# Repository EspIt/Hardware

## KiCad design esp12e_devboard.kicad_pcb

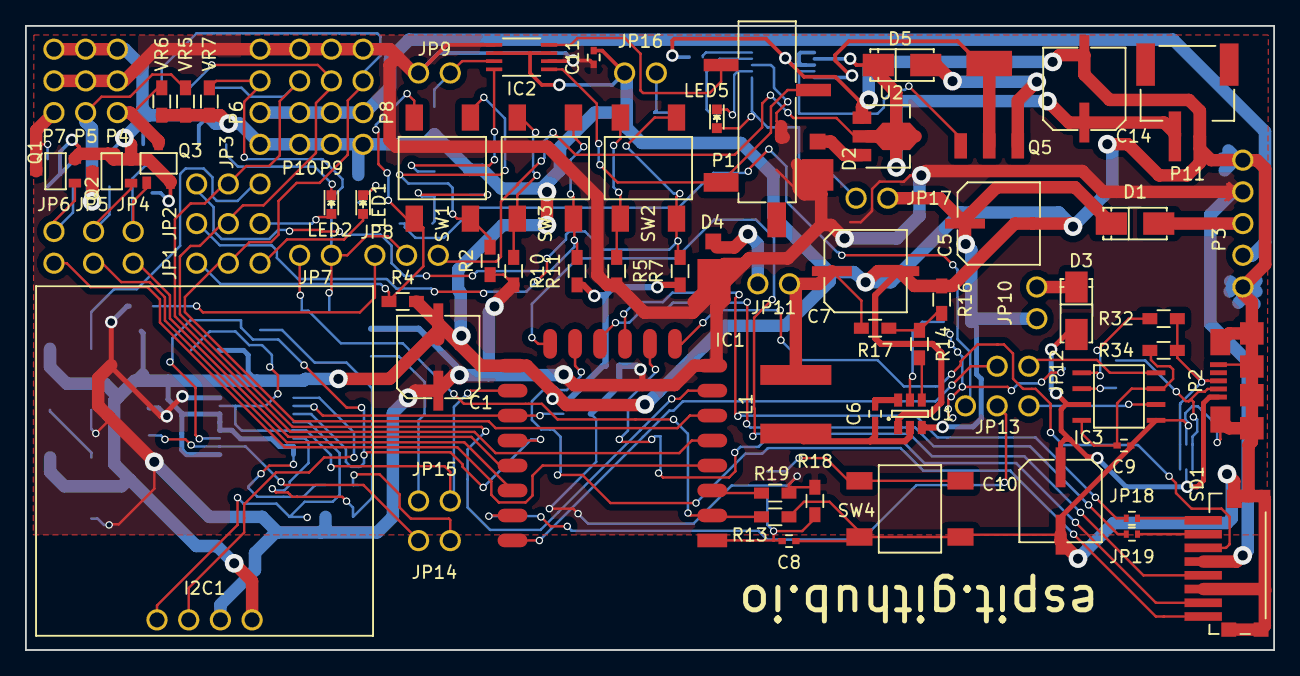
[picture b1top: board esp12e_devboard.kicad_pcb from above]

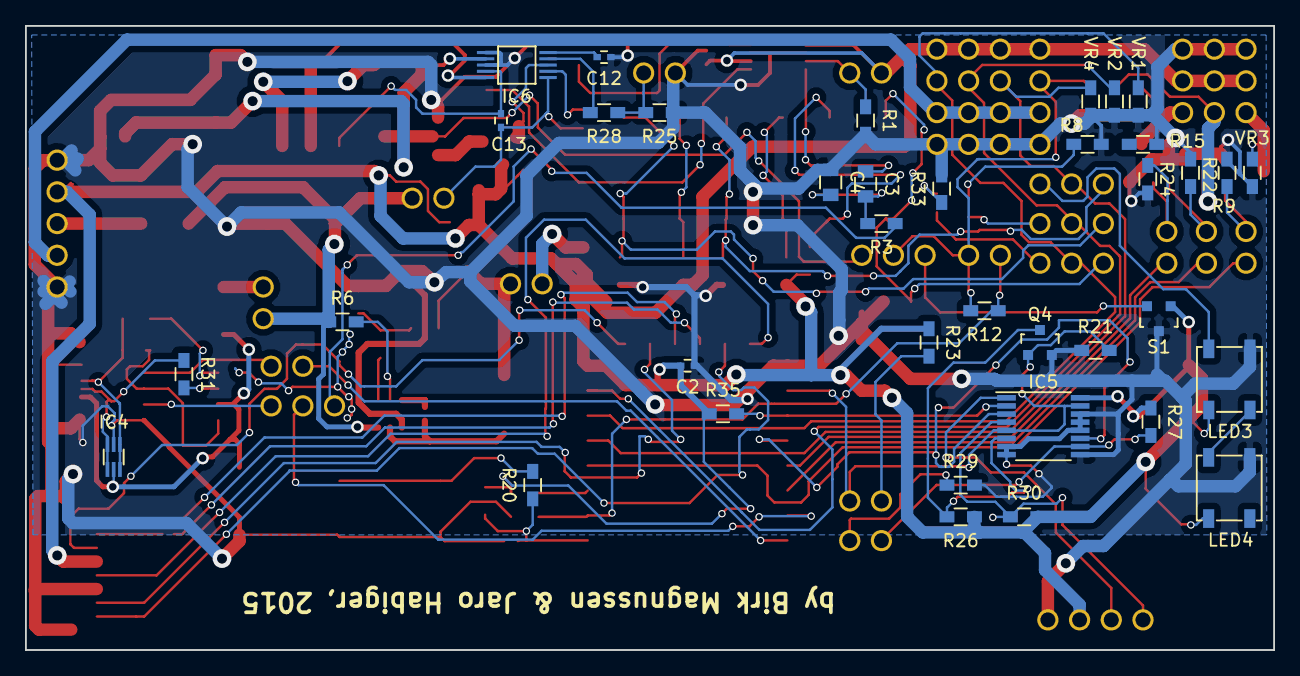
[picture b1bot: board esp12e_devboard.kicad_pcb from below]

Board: 2 copper layers, 100.0 x 50.0 mm, 117 parts (37 on the bottom side), 86 nets.

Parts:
C1, C5, C7, C10, C14: UWT1E101MCL1GS; UWT1E101MCL1GS_N
C2, C6, C8, C9, C11: CL05A105JQ5NNNC; C_0402
C3: CL21F334ZBFNNNE; C_0805
C4: FCA0805C104M-J2; C_0805
C12, C13: 100n_0603; C_0402
D1, D3, D5: SK34A-LTP; DO-214AC_N
D2, D4: UPS115UE3/TR7CT-ND; UPS115UE3_TR7
I2C1: IIC Serial 128X64; i2c
IC1: ESP12E
IC2: LM4906MM/NOPB; VSSOP-8_N
IC3: PL2303SA; SOP8
IC4: USBLC6_2SC6; SOT-666_N
IC5: CD74HC4316PWR; TSSOP-16_4.4x5mm_Pitch0.65mm
IC6: MAX1898EUB42; µMax
JP1, JP2, JP3, JP8, JP13: JUMPER3; Conn_3
JP4, JP5, JP6, JP7, JP9, JP10, JP11, JP12, JP14, JP15, JP16, JP17: JUMPER; Conn_2
JP18, JP19: 0; R_0402
L1: NR6028T4R7M
LED1, LED2, LED5: LED_0603; LED-0603
LED3, LED4: WS2812B; 5050
P1: SJ-3523-SMT-TR; SJ-3523-SMT-TR_N
P2: 10118192-0001LF; MicroUSB
P3: CONN_01X05; Conn_5
P4, P5, P7: CONN_01X03; Conn_3
P6, P8, P9, P10: CONN_01X04; Conn_4
P11: S2B-PH-SM4-TB(LF)(SN); PH_2
Q1, Q2, Q3: RSR030N06TL; TSMT3
Q4: 2N7002P; SOT-23
Q5: FCX717; SOT-223
R1, R4, R6, R7, R9, R11, R13, R21, R22, R24, R27: 100k; R_0603_HandSoldering
R2, R5, R10, R20: 1k; R_0603_HandSoldering
R3: 74; R_0603_HandSoldering
R8, R15, R33: 1.6k; R_0603_HandSoldering
R12: 400k; R_0603_HandSoldering
R14: 75k; R_0603_HandSoldering
R16: 13k; R_0603_HandSoldering
R17: 40.2k; R_0603_HandSoldering
R18, R19, R23, R26, R29, R30, R35: 10k; R_0603_HandSoldering
R25: 11k; R_0603_HandSoldering
R28: 3.5k; R_0603_HandSoldering
R31, R32: 27; R_0603_HandSoldering
R34: 1.5k; R_0603_HandSoldering
S1: MCP9700; SOT-23
SD1: SD-MICRO; 475710001
SW1, SW2, SW3, SW4: FSM4JSMA; FSM2JSMA
U1: MP1470; SOT-23-6
U2: AP7215-33YG-13; SOT89-3L
VR1, VR2, VR3, VR4, VR5, VR6, VR7: MLVA06V05C270; R_0603_HandSoldering

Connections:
+3V3: C1.1, C2.2, C11.1, D2.1, D4.1, I2C1.2, IC1.8, IC2.1, IC2.6, IC5.16, IC6.3, JP9.2, LED3.1, LED4.1, P3.4, P4.2, P5.2, P6.1, P7.2, P8.1, P9.1, P10.1, R2.2, R5.1, R10.1, R18.2, R19.2, R23.1, R26.1, R27.1, R30.2, R35.1, S1.1, SD1.4
+5V: D3.1, JP10.1
+12V: C5.1, D1.1, JP10.2, JP17.2, R6.1, U1.3
+BATT: C14.1, D5.1, IC6.7, JP8.1, P11.1, U2.2
AIn: JP7.2, JP8.2, P6.2, R12.2, VR7.1
Audio: JP13.3, R3.1
BOOT1: IC1.17, IC5.2, R35.2
BOOT2: IC1.18, IC5.3, IC5.11
GND: C1.2, C2.1, C4.1, C5.2, C7.2, C8.1, C9.1, C10.2, C11.2, C12.1, C14.2, I2C1.1, IC1.15, IC2.2, IC2.7, IC3.1, IC4.2, IC5.7, IC5.8, IC5.9, IC5.12, IC5.13, IC5.14, IC6.6, IC6.8, JP16.2, LED3.3, LED4.3, P2.5, P2.6, P3.1, P3.5, P4.1, P5.1, P6.4, P7.1, P8.4, P9.4, P10.4, P11.2, Q1.2, Q2.2, Q3.2, Q4.2, R1.2, R4.1, R7.1, R8.1, R9.2, R11.1, R13.1, R15.1, R16.1, R21.1, R22.2, R24.2, R25.1, R29.2, R33.2, S1.3, SD1.6, SD1.M1, SD1.M2, SD1.M3, SD1.M4, SD1.M5, SW4.2, U1.1, U2.1, VR1.2, VR2.2, VR3.2, VR4.1, VR5.2, VR6.2, VR7.2
GPIO1: IC1.6, JP1.2, P8.2, VR1.1
GPIO2: IC1.7, JP2.2, P9.2, VR2.1
GPIO3: IC1.5, JP3.2, P10.2, VR4.2
I2C_0: I2C1.4, IC5.4, R30.1
I2C_1: I2C1.3, IC5.1
I2C_TRIG: IC1.16, IC5.5, IC5.15, JP15.1, Q4.1, R21.2
LOut1: P4.3, Q3.3, VR6.1
LOut2: P5.3, Q2.3, VR5.1
LOut3: P7.3, Q1.3, VR3.1
unnamed: C3.1, IC2.4
unnamed: C3.2, C4.2, R3.2
unnamed: C6.1, L1.2, U1.2
unnamed: C6.2, U1.6
unnamed: C7.1, JP11.1, L1.1, R17.1
unnamed: C8.2, IC1.1, R18.1, R20.1
unnamed: C9.2, IC3.3, IC3.8, R34.1
unnamed: C10.1, D3.2, IC3.7, IC4.5, P2.1
unnamed: C12.2, IC6.5
unnamed: C13.1, IC6.9, Q5.1
unnamed: C13.2, IC6.1, JP17.1, LED5.2
unnamed: D2.2, U2.3
unnamed: D4.2, JP11.2
unnamed: D5.2, Q5.3
unnamed: IC1.2, JP7.1, R12.1, R13.2
unnamed: IC1.3, R19.1
unnamed: IC1.4, JP6.1
unnamed: IC1.9, SD1.3
unnamed: IC1.10, SD1.7
unnamed: IC1.11, JP18.1
unnamed: IC1.12, JP19.2
unnamed: IC1.13, SD1.8
unnamed: IC1.14, SD1.5
unnamed: IC1.19, JP4.1
unnamed: IC1.20, JP5.1
unnamed: IC2.3, JP9.1, R1.1
unnamed: IC2.5, P1.1, P1.4
unnamed: IC2.8, P1.5
unnamed: IC3.2, JP13.1
unnamed: IC3.4, JP12.2
unnamed: IC3.5, R32.2
unnamed: IC3.6, R31.2
unnamed: IC4.1, IC4.6, P2.3, R32.1, R34.2
unnamed: IC4.3, IC4.4, P2.2, R31.1
unnamed: IC5.6, Q4.3, R26.2
unnamed: IC5.10, JP14.1, R27.2
unnamed: IC6.2, LED5.1
unnamed: IC6.4, R28.2
unnamed: IC6.10, Q5.2
unnamed: JP1.1, LED1.2
unnamed: JP1.3, R4.2, SW1.2
unnamed: JP2.1, LED2.2
unnamed: JP2.3, R7.2, SW2.1
unnamed: JP3.3, R11.2, SW3.1
unnamed: JP4.2, Q3.1, R24.1
unnamed: JP5.2, Q2.1, R22.1
unnamed: JP6.2, Q1.1, R9.1
unnamed: JP8.3, S1.2
unnamed: JP14.2, R29.1
unnamed: JP15.2, R23.2
unnamed: JP16.1, R25.2, R28.1
unnamed: JP18.2, SD1.1
unnamed: JP19.1, SD1.2
unnamed: LED1.1, R33.1
unnamed: LED2.1, R8.2
unnamed: LED3.2, LED4.4
unnamed: R2.1, SW1.1
unnamed: R5.2, SW2.2
unnamed: R6.2, U1.5
unnamed: R10.2, SW3.2
unnamed: R14.1, R16.2, R17.2
unnamed: R14.2, U1.4
unnamed: R20.2, SW4.1
RxD_USB: IC1.22, JP12.1
TxD_USB: IC1.21, JP13.2
VIn: D1.2, P3.3
VUser: P3.2, P6.3, P8.3, P9.3, P10.3
led: JP3.1, LED3.4

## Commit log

2015-12-22 Required Footprints
2015-12-22 Gerber Files
2015-12-22 KiCad files
2015-12-22 Wrong boot-resistor value
